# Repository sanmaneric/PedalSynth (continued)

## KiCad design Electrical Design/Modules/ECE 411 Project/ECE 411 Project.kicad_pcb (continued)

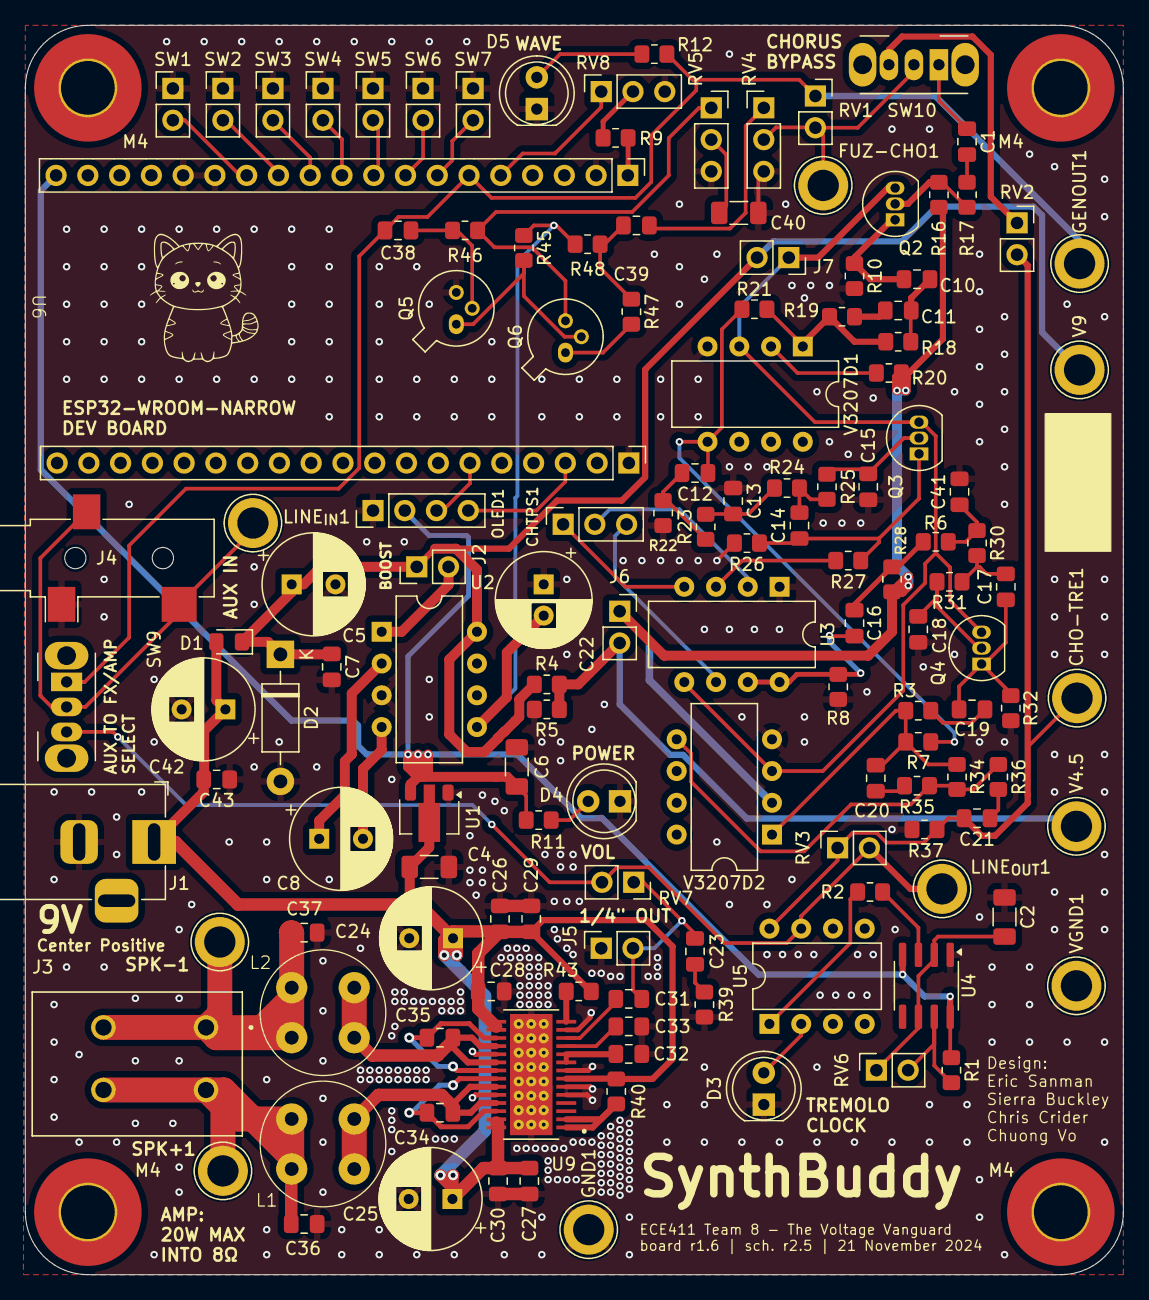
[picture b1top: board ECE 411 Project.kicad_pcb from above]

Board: 2 copper layers, 87.8 x 99.9 mm, 142 parts (0 on the bottom side), 85 nets.

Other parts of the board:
M4, M4#2, M4#3, M4#4: MountingHole_4.3mm_M4_Pad_TopBottom

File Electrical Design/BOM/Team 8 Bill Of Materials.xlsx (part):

|  | Bill Of Materials for: Team 8 (Voltage Vanguards)
 |  | Last modified: 13 November 2024
 |  | PCB version: 2
 |  | BOM revision: 2 |  | P/NP | = Place/Not Place (components marked NP are not stuffed on the board)
QA | QA Comments | Cnt | Part References | P/NP | Mfg | Mfg PN | Description | Dist | Dist Part Number | Cost Ea. | Cost Total
OK |  | 2.0 | C8, C22 | P | Nichicon | UVR2C100MPD | 10 µF 160 V Aluminum Electrolytic Capacitors Radial, Can 2000 Hrs @ 85°C | Digi-Key | 493-1161-ND | 0.33 | 0.66
OK |  | 1.0 | C5 | P | Nichicon | UVK2A470MPD | 47 µF 100 V Aluminum Electrolytic Capacitors Radial, Can 2000 Hrs @ 85°C | Digi-Key | 493-6068-ND | 0.32 | 0.32
OK |  | 1.0 | C11 | P | KYOCERA AVX | KGM21NR71H683KT | 0.068 µF ±10% 50V Ceramic Capacitor X7R 0805 (2012 Metric) | Digi-Key | 478-KGM21NR71H683KTCT-ND | 0.1 | 0.1
OK |  | 1.0 | C2 | P | Samsung Electro-Mechanics | CL31B475KAHNNNE | 4.7 µF ±10% 25V Ceramic Capacitor X7R 1206 (3216 Metric) | Digi-Key | 1276-1055-2-ND | 0.17 | 0.17
OK |  | 2.0 | C4,C6 | P | Samsung Electro-Mechanics | CL21B106KOQNNNG | 10 µF ±10% 25V Ceramic Capacitor X7R 1206 (3216 Metric) | Digi-Key | 1276-1055-1-ND | 0.17 | 0.34
Check | check part values with Sierra | 2.0 | C1, C10 | P | Samsung Electro-Mechanics | CL21B473KBCNNNC | 0.047 µF ±10% 50V Ceramic Capacitor X7R 0805 (2012 Metric) | Digi-Key | 1276-1250-2-ND | 0.1 | 0.2
OK |  | 1.0 | C12 | P | Samsung Electro-Mechanics | CL21B334KBFNNNE | 0.33 µF ±10% 50V Ceramic Capacitor X7R 0805 (2012 Metric) | Digi-Key | 1276-1250-1-ND | 0.1 | 0.1
OK |  | 3.0 | C7,C26,C27 | P | Samsung Electro-Mechanics | CL21B104KCFNNNE | 0.1 µF ±10% 100V Ceramic Capacitor X7R 0805 (2012 Metric) | Digikey | 1276-6840-1-ND | 0.1 | 0.3
OK |  | 1.0 | C20 | P | KEMET | C0805C682J1GEC7210 | 6800 pF ±5% 100V Ceramic Capacitor C0G, NP0 0805 (2012 Metric) | Digi-Key | 399-C0805C682J1GEC7210CT-ND | 0.27 | 0.27
OK |  | 2.0 | C15,C18 | P | KEMET | C0805C471K5RAC7800 | 470 pF ±10% 50V Ceramic Capacitor X7R 0805 (2012 Metric) | Digi-Key | 399-C0805C471K5RAC7800TR-ND | 0.1 | 0.2
OK |  | 2.0 | C16,C19 | P | KEMET | C0805C333K1RECAUTO | 0.033 µF ±10% 100V Ceramic Capacitor X7R 0805 (2012 Metric) | Digi-Key | 399-C0805C471K5RAC7800CT-ND | 0.1 | 0.2
OK |  | 2.0 | C13,C41 | P | KEMET | C0805C332K1RECAUTO | 3300 pF ±10% 100V Ceramic Capacitor X7R 0805 (2012 Metric) | Digi-Key | 399-C0805C332K1RECAUTOCT-ND | 0.26 | 0.52
OK |  | 2.0 | C14,C17 | P | KEMET | C0402C822K1RACAUTO | 8200 pF ±10% 100V Ceramic Capacitor X7R 0402 (1005 Metric) | Digi-Key | 399-C0402C822K1RACAUTOCT-ND | 0.21 | 0.42
OK |  | 2.0 | C34,C35 | P | Samsung Electro-Mechanics | CL21B474KAFNNNE | 0.47 µF ±10% 25V Ceramic Capacitor X7R 0805 (2012 Metric) | Digi-Key | 1276-1074-2-ND | 0.1 | 0.2
OK |  | 7.0 | C21,C23,C28,C32,C36,C37,C43 | P | Samsung Electro-Mechanics | CL21B105KAFNNNE | 1 µF ±10% 25V Ceramic Capacitor X7R 0805 (2012 Metric) | Digi-Key | 1276-1066-1-ND | 0.1 | 0.7
OK |  | 3.0 | C42,C24,C25 | P | Nichicon | UVR1H101MPD1TD | 100 µF 50 V Aluminum Electrolytic Capacitors Radial, Can 2000 Hrs @ 85°C | Digi-Key | 493-5916-1-ND | 0.34 | 1.02
OK |  | 1.0 | C40 | P | Cal-Chip Electronics, Inc. | GMC31X7R226M10NT | CAP1206 X7R 22UF 20% 10V | Digi-Key | 4713-GMC31X7R226M10NTCT-ND | 0.27 | 0.27
OK |  | 1.0 | C39 | P | KEMET | C0805C103K5RACTU | 10000 pF ±10% 50V Ceramic Capacitor X7R 0805 (2012 Metric) | Digi-Key | 399-C0805C103K5RACTUCT-ND | 0.1 | 0.1
OK |  | 1.0 | C38 | P | Samsung Electro-Mechanics | CL21B225KPFNNNE | 2.2 µF ±10% 10V Ceramic Capacitor X7R 0805 (2012 Metric) | Digi-Key | 1276-1188-1-ND | 0.1 | 0.1
OK |  | 2.0 | C33,C31 | P | YAGEO | CC0805KRX7R9BB104 | 0.1 µF ±10% 50V Ceramic Capacitor X7R 0805 (2012 Metric) | Digi-Key | 311-1140-1-ND | 0.1 | 0.2
OK |  | 2.0 | C29,C30 | P | Samsung Electro-Mechanics | CL21B102KCANNNC | 1000 pF ±10% 100V Ceramic Capacitor X7R 0805 (2012 Metric) | Digi-Key | 1276-1169-1-ND | 0.1 | 0.2
Hold | hold for testing to find PN | 3.0 | V3207D1,V3207D2,U3 | P | Coolaudio | V3207D - BBD IC | V3207D - BBD IC | stompboxparts | IC-400-1033 | 3.7 | 11.1
OK |  | 1.0 | U11 | P | Espressif | ESP32-WROOM | ESP-WROOM-32 ESP32 ESP-32S Development Board 2.4GHz Dual-Mode WiFi + Bluetooth 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 | Amazon | Amazon | 3.0 | 3
OK |  | 1.0 | U9 | P | TI | TPA3136D2PWPR | IC AMP CLASS D STER 10W 28HTSSOP | Digi-Key | 296-44601-1-ND | 1.31 | 1.31
OK |  | 1.0 | U5 | P | Lite-on Inc. | LTV-827 | OPTOISOLATOR 5KV 2CH TRANS 8-DIP | Digi-Key | 160-1368-5-ND | 0.64 | 0.64
OK |  | 1.0 | U4 | P | TI | NE555D | 555 Type, Timer/Oscillator (Single) IC 100kHz 8-SOIC | Digi-Key | 296-16792-ND | 0.89 | 0.89
OK |  | 1.0 | U2 | P | TI | LT1054IDW | Charge Pump Switching Regulator IC Positive or Negative Adjustable (Fixed) 3.5V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 | Digi-Key | 296-9592-5-ND | 2.81 | 2.81
OK |  | 1.0 | U1 | P | UMW | HT7333-A | Linear Voltage Regulator IC Positive Fixed 1 Output 150mA SOT-89-3 | Digi-Key | 4518-HT7333-ACT-ND | 0.65 | 0.65
OK |  | 9.0 | SW1,SW2,SW3,SW4,SW5,SW6,SW7,SW8, J2 | P | Adam Tech | PH1-02-UA | CONN HEADER VERT 2POS 2.54MM | Digi-Key | 2057-PH1-02-UA-ND | 0.1 | 0.9
OK |  | 6.0 | RV1,RV2,RV3,RV4,RV5,RV6 | P | Adam Tech | PH1-03-UA | CONN HEADER VERT 3POS 2.54MM | Digi-Key | 2057-PH1-03-UA-ND | 0.1 | 0.6
OK |  | 1.0 | R47 | P | YAGEO | RC0805JR-078K2L | 8.2 kOhms ±5% 0.125W, 1/8W Chip Resistor 0805 (2012 Metric) Moisture Resistant 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 | Digi-Key | 311-8.2KARCT-ND | 0.1 | 0.1
OK |  | 1.0 | R45 | P | Stackpole Electronics Inc | RMCF0805JT33K0 | 33 kOhms ±5% 0.125W, 1/8W Chip Resistor 0805 (2012 Metric) Automotive AEC-Q200 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 | Digi-Key | RMCF0805JT33K0CT-ND | 0.1 | 0.1
OK |  | 1.0 | R39 | P | YAGEO | RC0805FR-071KL | 1 kOhms ±1% 0.125W, 1/8W Chip Resistor 0805 (2012 Metric) Moisture Resistant Th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 | Digi-Key | 311-1.00KCRCT-ND | 0.1 | 0.1
OK |  | 2.0 | R36,R48 | P | TE Connectivity Passive Product | CRGCQ0805J470R | 470 Ohms ±5% 0.125W, 1/8W Chip Resistor 0805 (2012 Metric) Automotive AEC-Q200,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 | Digi-Key | A130132CT-ND | 0.1 | 0.2
OK |  | 1.0 | R28 | P | Panasonic Electronic Components | ERJ-6GEYJ334V | 330 kOhms ±5% 0.125W, 1/8W Chip Resistor 0805 (2012 Metric) Automotive AEC-Q200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 | Digi-Key | P330KACT-ND | 0.1 | 0.1
OK |  | 1.0 | R27 | P | Vishay Dale | CRCW08054K70FKEAC | 4.7 kOhms ±1% 0.125W, 1/8W Chip Resistor 0805 (2012 Metric) Thick Film | Digi-Key | 541-4131-1-ND | 0.1 | 0.1
OK |  | 5.0 | R22,R37,R40,R43,R46 | P | YAGEO | RC0805FR-07100KL | 100 kOhms ±1% 0.125W, 1/8W Chip Resistor 0805 (2012 Metric) Moisture Resistant 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 | Digi-Key | 311-100KCRCT-ND | 0.1 | 0.5
OK |  | 1.0 | R16 | P | YAGEO | RC0805JR-071ML | 1 MOhms ±5% 0.125W, 1/8W Chip Resistor 0805 (2012 Metric) Moisture Resistant Th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 | Digi-Key | 311-1.0MARCT-ND | 0.1 | 0.1
OK |  | 1.0 | R8 | P | KOA Speer Electronics, Inc. | RK73B2ATTD563J | 56 kOhms ±5% 0.25W, 1/4W Chip Resistor 0805 (2012 Metric) Automotive AEC-Q200 T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 | Digi-Key | 2019-RK73B2ATTD563JCT-ND | 0.1 | 0.1
OK |  | 15.0 | R4,R5,R6,R10,R17,R19,R20,R23,R24,R25,R26,R30,R31,R32,R35 | P | Stackpole Electronics Inc | RMCF0805FT10K0 | 10 kOhms ±1% 0.125W, 1/8W Chip Resistor 0805 (2012 Metric) Automotive AEC-Q200 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 | Digi-Key | RMCF0805FT10K0CT-ND | 0.1 | 1.5
OK |  | 5.0 | R3,R7,R18,R21,R34 | P | Stackpole Electronics Inc | RMCF0805JT47K0 | 47 kOhms ±5% 0.125W, 1/8W Chip Resistor 0805 (2012 Metric) Automotive AEC-Q200 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 | Digi-Key | RMCF0805JT47K0CT-ND | 0.1 | 0.5
OK |  | 2.0 | R1,R2 | P | TE Connectivity Passive Product | CRG0805F1K2 | 1.2 kOhms ±1% 0.125W, 1/8W Chip Resistor 0805 (2012 Metric) Thick Film | Digi-Key | A126346CT-ND | 0.1 | 0.2
OK |  | 1.0 | Q5,Q6 | P | PMMCON | AC128 | Pcs of 2 New, AC128 PNP Transistor | Amazon | Amazon | 12.15 | 12.15
OK |  | 3.0 | Q2,Q3,Q4 | P | Diotec Semiconductor | 2N3904 | Bipolar (BJT) Transistor NPN 40 V 200 mA 300MHz 625 mW Through Hole TO-92 | Digi-Key | 4878-2N3904CT-ND | 0.1 | 0.3
Note | modify kicad footprint | 1.0 | OLED-Header | P | Adam Tech | PH1-04-UA | CONN HEADER VERT 4POS 2.54MM | Digi-Key | 2057-PH1-04-UA-ND | 0.1 | 0.1
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
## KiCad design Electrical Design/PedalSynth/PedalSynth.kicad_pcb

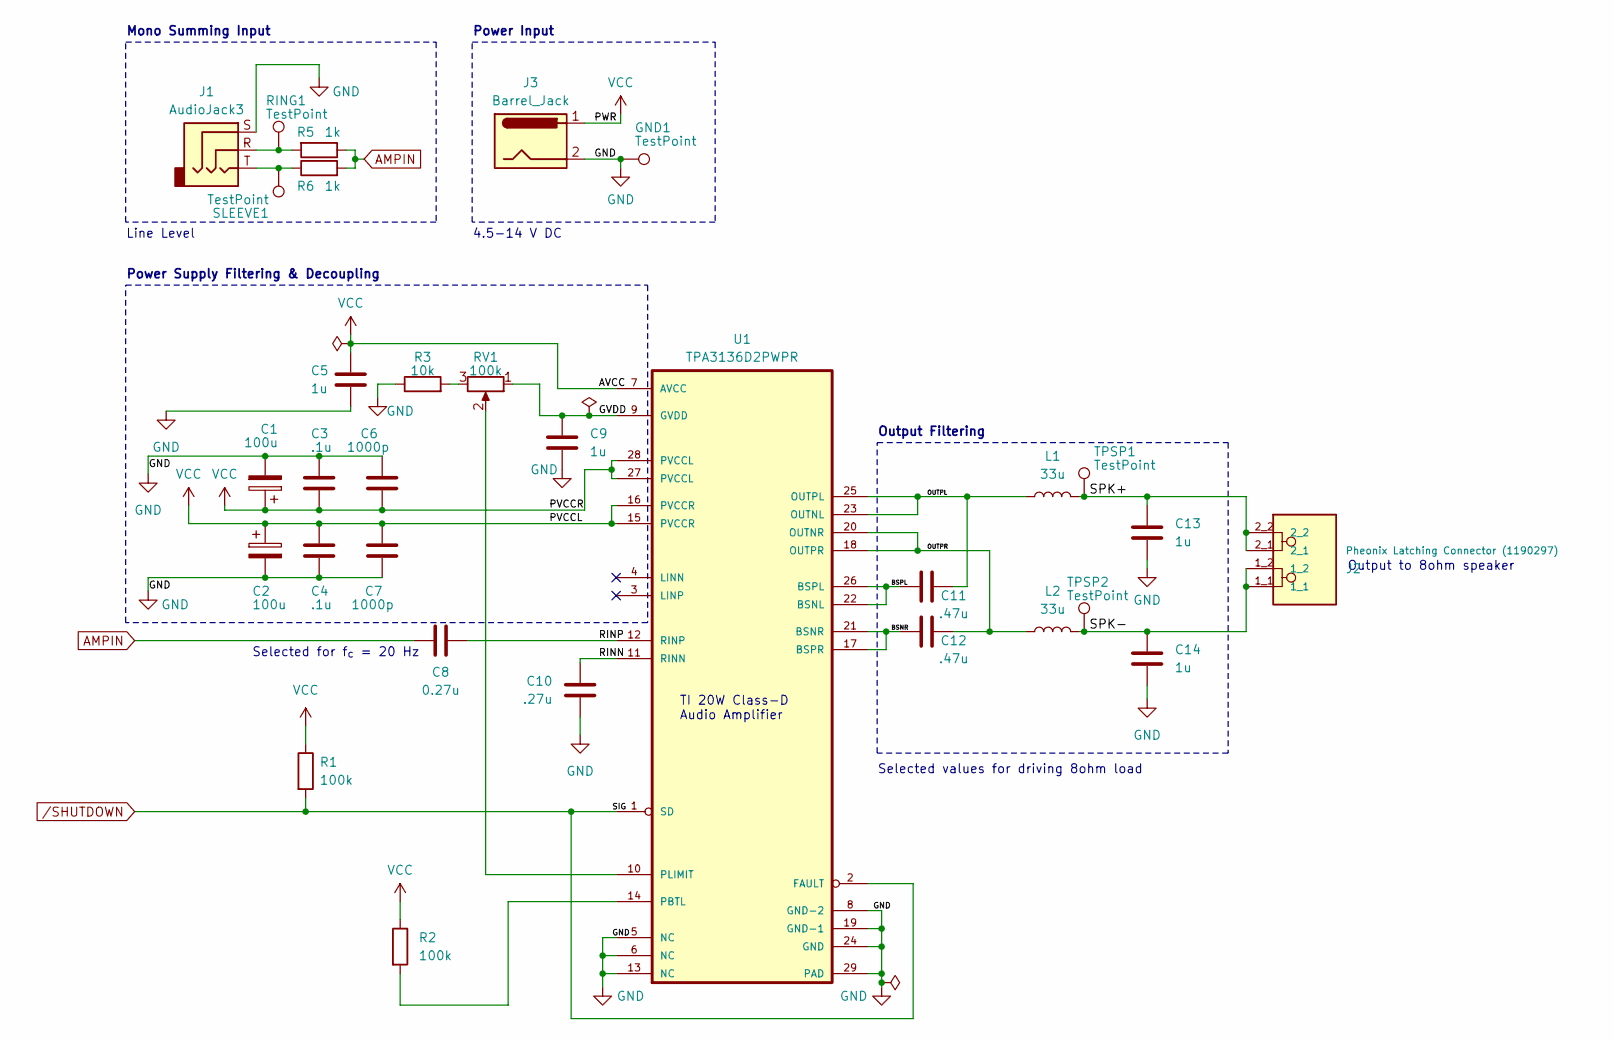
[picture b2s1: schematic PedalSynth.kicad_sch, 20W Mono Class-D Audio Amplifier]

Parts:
C1, C2: 100u; CP_Radial_D8.0mm_P3.50mm
C3, C4: .1u; C_0805_2012Metric_Pad1.18x1.45mm_HandSolder
C5, C9, C13, C14: 1u; C_0805_2012Metric_Pad1.18x1.45mm_HandSolder
C6, C7: 1000p; C_0402_1005Metric_Pad0.74x0.62mm_HandSolder
C8: 0.27u; C_0402_1005Metric_Pad0.74x0.62mm_HandSolder
C10: .27u; C_0402_1005Metric_Pad0.74x0.62mm_HandSolder
C11, C12: .47u; C_0402_1005Metric_Pad0.74x0.62mm_HandSolder
GND1: TestPoint; TestPoint_Bridge_Pitch2.0mm_Drill0.7mm
J1: AudioJack3; Jack_3.5mm_CUI_SJ-3523-SMT_Horizontal
J2: Pheonix Latching Connector (1190297); PHOENIX_1190297; PARTREV 03.11.2020
J3: Barrel_Jack; BarrelJack_Wuerth_6941xx301002
L1, L2: 33u; IND_VLS6045AF-330M
R1, R2: 100k; R_0402_1005Metric_Pad0.72x0.64mm_HandSolder
R3: 10k; R_0402_1005Metric_Pad0.72x0.64mm_HandSolder
R5, R6: 1k; R_0402_1005Metric_Pad0.72x0.64mm_HandSolder
RING1: TestPoint; TestPoint_Bridge_Pitch2.0mm_Drill0.7mm
RV1: 100k; Potentiometer_Bourns_3386P_Vertical
SLEEVE1: TestPoint; TestPoint_Bridge_Pitch2.0mm_Drill0.7mm
TPSP1, TPSP2: TestPoint; TestPoint_Bridge_Pitch2.0mm_Drill0.7mm
U1: TPA3136D2PWPR; IC_TPS61196PWPRQ1

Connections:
/BSNR: C12.1, U1.17 (BSPR), U1.21 (BSNR)
/BSPL: C11.1, U1.22 (BSNL), U1.26 (BSPL)
/GVDD: C9.2, RV1.1, U1.9 (GVDD)
/OUTPL: C11.2, L1.1, U1.23 (OUTNL), U1.25 (OUTPL)
/OUTPR: C12.2, L2.1, U1.18 (OUTPR), U1.20 (OUTNR)
/RINN: C10.1, U1.11 (RINN)
/RINP: C8.1, U1.12 (RINP)
/SPK+: C13.1, J2.2_1, J2.2_2, L1.2, TPSP1.1
/SPK-: C14.1, J2.1_1, J2.1_2, L2.2, TPSP2.1
AMPIN: C8.2, R5.1, R6.2
GND: C1.2, C2.2, C3.1, C4.2, C5.2, C6.1, C7.2, C9.1, C10.2, C13.2, C14.2, GND1.1, J1.S, J3.2, R3.1, U1.5 (NC), U1.6 (NC), U1.8 (GND-2), U1.13 (NC), U1.19 (GND-1), U1.24 (GND), U1.29 (PAD)
unnamed: J1.R, R5.2, RING1.1
unnamed: J1.T, R6.1, SLEEVE1.1
unnamed: R3.2, RV1.3
unnamed: R2.2, U1.14 (PBTL)
unnamed: RV1.2, U1.10 (PLIMIT)
VCC: C1.1, C2.1, C3.2, C4.1, C5.1, C6.2, C7.1, J3.1, R1.1, R2.1, U1.7 (AVCC), U1.15 (PVCCR), U1.16 (PVCCR), U1.27 (PVCCL), U1.28 (PVCCL)
/SHUTDOWN: R1.2, U1.1 (SD), U1.2 (FAULT)

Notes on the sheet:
Mono Summing Input
Selected values for driving 8ohm load
Line Level
Selected for f_{c} = 20 Hz
Output to 8ohm speaker
Power Supply Filtering & Decoupling
Power Input
TI 20W Class-D Audio Amplifier
Output Filtering
4.5-14 V DC

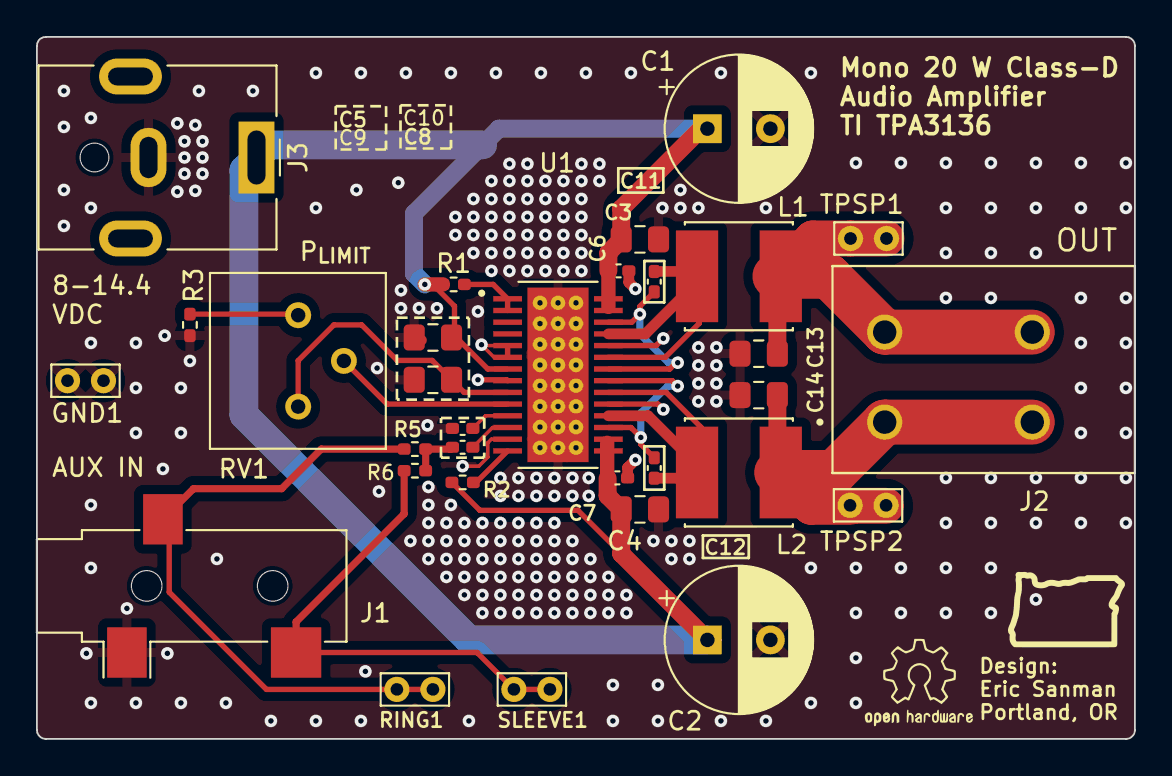
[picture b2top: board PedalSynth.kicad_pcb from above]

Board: 2 copper layers, 61.0 x 39.0 mm, 31 parts (0 on the bottom side), 18 nets.

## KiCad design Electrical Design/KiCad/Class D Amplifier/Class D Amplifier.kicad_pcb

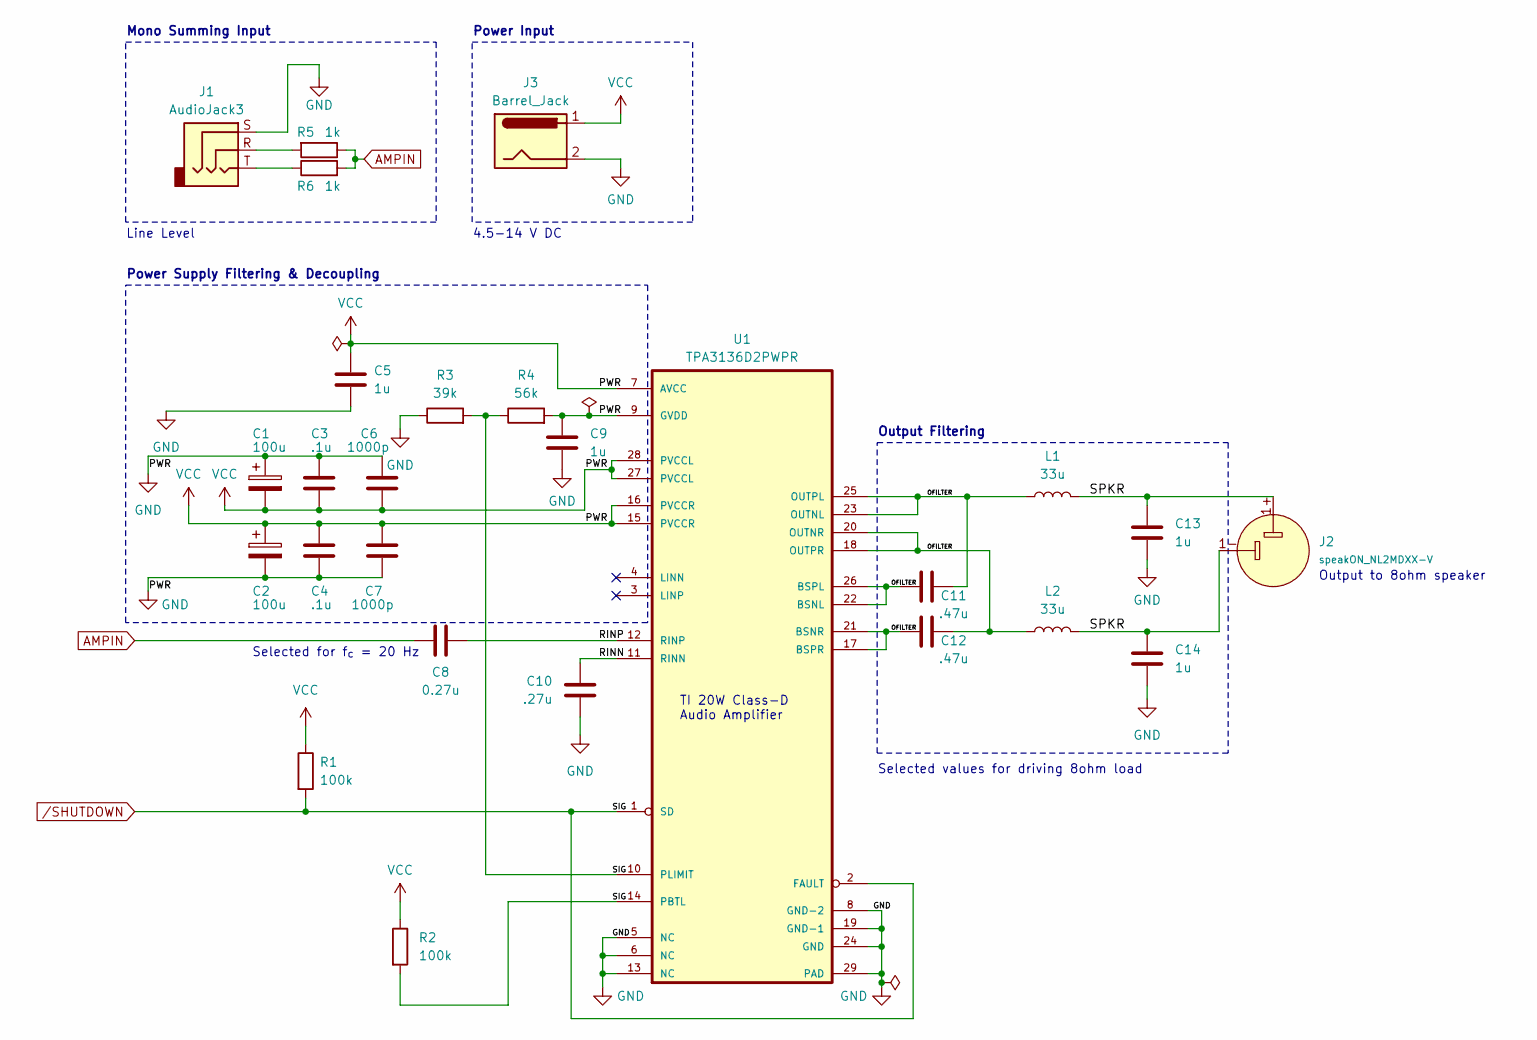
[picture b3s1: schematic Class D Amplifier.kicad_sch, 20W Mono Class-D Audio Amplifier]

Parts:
C1, C2: 100u; C_0805_2012Metric_Pad1.18x1.45mm_HandSolder
C3, C4: .1u; C_0805_2012Metric_Pad1.18x1.45mm_HandSolder
C5, C9, C13, C14: 1u; C_0805_2012Metric_Pad1.18x1.45mm_HandSolder
C6, C7: 1000p; C_0402_1005Metric_Pad0.74x0.62mm_HandSolder
C8: 0.27u; C_0402_1005Metric_Pad0.74x0.62mm_HandSolder
C10: .27u; C_0402_1005Metric_Pad0.74x0.62mm_HandSolder
C11, C12: .47u; C_0402_1005Metric_Pad0.74x0.62mm_HandSolder
J1: AudioJack3; Jack_3.5mm_CUI_SJ-3523-SMT_Horizontal
J2: speakON_NL2MDXX-V; Jack_speakON_Neutrik_NL2MDXX-H-3_Horizontal
J3: Barrel_Jack; BarrelJack_CUI_PJ-063AH_Horizontal
L1, L2: 33u; L_Taiyo-Yuden_MD-3030
R1, R2: 100k; R_0402_1005Metric_Pad0.72x0.64mm_HandSolder
R3: 39k; R_0402_1005Metric_Pad0.72x0.64mm_HandSolder
R4: 56k; R_0402_1005Metric_Pad0.72x0.64mm_HandSolder
R5, R6: 1k; R_0402_1005Metric_Pad0.72x0.64mm_HandSolder
U1: TPA3136D2PWPR; IC_TPS61196PWPRQ1

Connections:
/OFILTER: C11.1, C11.2, C12.1, C12.2, L1.1, L2.1, U1.17 (BSPR), U1.18 (OUTPR), U1.20 (OUTNR), U1.21 (BSNR), U1.22 (BSNL), U1.23 (OUTNL), U1.25 (OUTPL), U1.26 (BSPL)
/RINN: C10.1, U1.11 (RINN)
/RINP: C8.1, U1.12 (RINP)
/SPKR: C13.1, C14.1, J2.1+, J2.1-, L1.2, L2.2
AMPIN: C8.2, R5.1, R6.2
GND: C1.1, C1.2, C2.1, C2.2, C3.1, C3.2, C4.1, C4.2, C5.1, C5.2, C6.1, C6.2, C7.1, C7.2, C9.1, C9.2, C10.2, C13.2, C14.2, J1.S, J3.1, J3.2, R1.1, R2.1, R3.1, R4.2, U1.5 (NC), U1.6 (NC), U1.7 (AVCC), U1.8 (GND-2), U1.9 (GVDD), U1.13 (NC), U1.15 (PVCCR), U1.16 (PVCCR), U1.19 (GND-1), U1.24 (GND), U1.27 (PVCCL), U1.28 (PVCCL), U1.29 (PAD)
unnamed: J1.R, R5.2
unnamed: J1.T, R6.1
/SHUTDOWN: R1.2, R2.2, R3.2, R4.1, U1.1 (SD), U1.2 (FAULT), U1.10 (PLIMIT), U1.14 (PBTL)

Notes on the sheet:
Mono Summing Input
Selected values for driving 8ohm load
Line Level
Selected for f_{c} = 20 Hz
Output to 8ohm speaker
Power Supply Filtering & Decoupling
Power Input
TI 20W Class-D Audio Amplifier
Output Filtering
4.5-14 V DC

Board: 2 copper layers, 26 parts (0 on the bottom side), 9 nets, no tracks yet.

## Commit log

2024-10-17 Create Diagrams
2024-10-17 moving files around
2024-10-17 readme setup
2024-10-18 more files!
2024-10-18 add Class D amplifier
2024-10-18 generate amplifier schematic
2024-10-18 class D schematic update
2024-10-18 update nets
2024-10-20 Create PCB files
2024-10-20 pushing PCB changes
2024-10-20 Layout improvements for amp
2024-10-20 Update readme markdown
2024-10-20 fix folder typo
2024-10-21 Upload of both Png and .drawio drawings of the diagrams
2024-10-21 board changes
2024-10-21 add PDS, modified amp footprint, organizational changes
2024-10-21 change readme
2024-10-21 format fix
2024-10-21 update structure
2024-10-22 weekly reports added
2024-10-22 getting kicad organized
    renamed root schematic, creating sub schematic for amplifier
2024-10-23 add kicad corner
2024-10-23 update via stitching
2024-10-24 update to v8
2024-10-24 Module Schematics for Parts of overall Project
2024-10-24 update amp schematic and pcb
2024-10-25 r1.0 amp pcb
2024-10-28 added progress report for last week
2024-10-28 update kicad corner
2024-10-28 typo fix
2024-10-28 test
2024-10-28 said hello
    yes
2024-10-28 reference materials for chorus effect
2024-10-28 Chorus Schematic Upload
2024-10-28 Noise Filter schematic with component Values
2024-10-28 datasheets
2024-10-28 Added in Specific Op amp model.
2024-10-28 Fuzz Schematic Upload
2024-10-30 Entire Preliminary Schematic Project Folder
2024-10-30 Minor changes to schematic wiring
2024-10-30 Final Touches to Preliminary Schematic
    Created Symbol for Small OLED screen and finalized input/output connections for each module
2024-10-31 revision number
2024-10-31 file opening
2024-10-31 Update fp-info-cache
2024-10-31 nothing changing
2024-11-02 rev1 for PDS, level 0 diagram
2024-11-02 rev1 level 1 diagram
2024-11-03 kicad business
2024-11-04 no change
2024-11-04 Commit for Various Things
    - Revised L1 Block Diagram
    - Revision 1.1 of the PDS
    - Version 1.0 of the Gantt Chart
2024-11-04 amp changes
2024-11-04 update prog report file names
2024-11-04 prog update
2024-11-04 update progress report
2024-11-04 Version 1 of Project Gantt Chart
2024-11-04 update stuff
2024-11-05 Set up Week 3 Progress Report based on Template
    Still needs to be cleaned up with additional things added.
2024-11-05 Reformatted Week 4 and 5 Weekly Reports
2024-11-07 added fuzz and chorus breadboard photos
2024-11-07 no update
2024-11-07 add psu and fix schematic
2024-11-07 filter changes
2024-11-07 schematic, start layout
2024-11-07 export pdfs
2024-11-07 project package(Uploaded to Canvas!)
2024-11-07 combined effects rev 0
2024-11-07 progress report updates
2024-11-08 update kicad
2024-11-08 recent progress report
2024-11-08 progress photo
2024-11-12 level 0 diagram rev 2 for functional decomp
2024-11-12 whyyy
2024-11-12 level 1 diagram, functional decomp
2024-11-13 update BOM
2024-11-13 bom changes
2024-11-13 added video and pic of fuzz
2024-11-14 Created Bill of Materials for Project
2024-11-14 add switch to schematic
2024-11-14 PCB V2!!!
2024-11-14 DRAFT PACKAGE
2024-11-14 Compiled all individual Progress reports into a singular running document
2024-11-15 oled test & schematic update
2024-11-15 schematic changes
2024-11-15 no change :)
2024-11-16 schematic update
2024-11-17 progress report update
2024-11-18 Updated week 6 and 7 Contributions
2024-11-18 pcb amp revision
2024-11-18 pcb redo b2.1
2024-11-18 new space-optimized PCB layout
2024-11-18 add testpoints
2024-11-19 update diode footptint, rounding edge cuts, some stitching
2024-11-19 pcb finalization
2024-11-19 pcb madness
2024-11-20 adding chorus test poiunts, touch ups
2024-11-21 FINAL DESIGN PACKAGE
2024-11-21 remove build folder to appease andrew
2024-11-21 sierra progress update and dates for the next 3
2024-11-21 update readme page
2024-11-22 minor formatting updates
2024-11-22 add label to U6
2024-12-05 Upload of Test Plan
2024-12-11 Chris' portion of status update
    (didnt save before when I committed)
2024-12-12 Last Additions to the Weekly Progress Reports for the Team
2024-12-12 none
2024-12-12 rev1.2
2024-12-12 Updated Gantt Chart to reflect current progress
2024-12-13 test wpr format changes
2024-12-13 PWM Signal and OLED Code
2024-12-13 Changed frequencies to reflect chord progression from C3 to B3
2024-12-13 Fixed Test Plan Formating
2024-12-13 Updating Task on Gantt
2024-12-13 Finalized SynthBuddy Code
